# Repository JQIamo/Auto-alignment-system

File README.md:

# Source Code for Autoalignment System

This git repository contains the entire source code for the autoalignment
system described in {link to the paper}. It includes:

- `src/`: The firmware for the microcontroller (Teensy 4.1).
- `scripts/`: The python scripts, run on a host PC, to communicate with the microcontroller
  for manual control and diagnostic purposes.
- `calibration/`: A Jupyter notebook that calculate the $A$ matrix from calibration data.
-  `eagle/`: Eagle schematic and board files for fabricating the main control board and the detector boards.

Instructions for how to compile and use the source code are documented in each
individual folder.

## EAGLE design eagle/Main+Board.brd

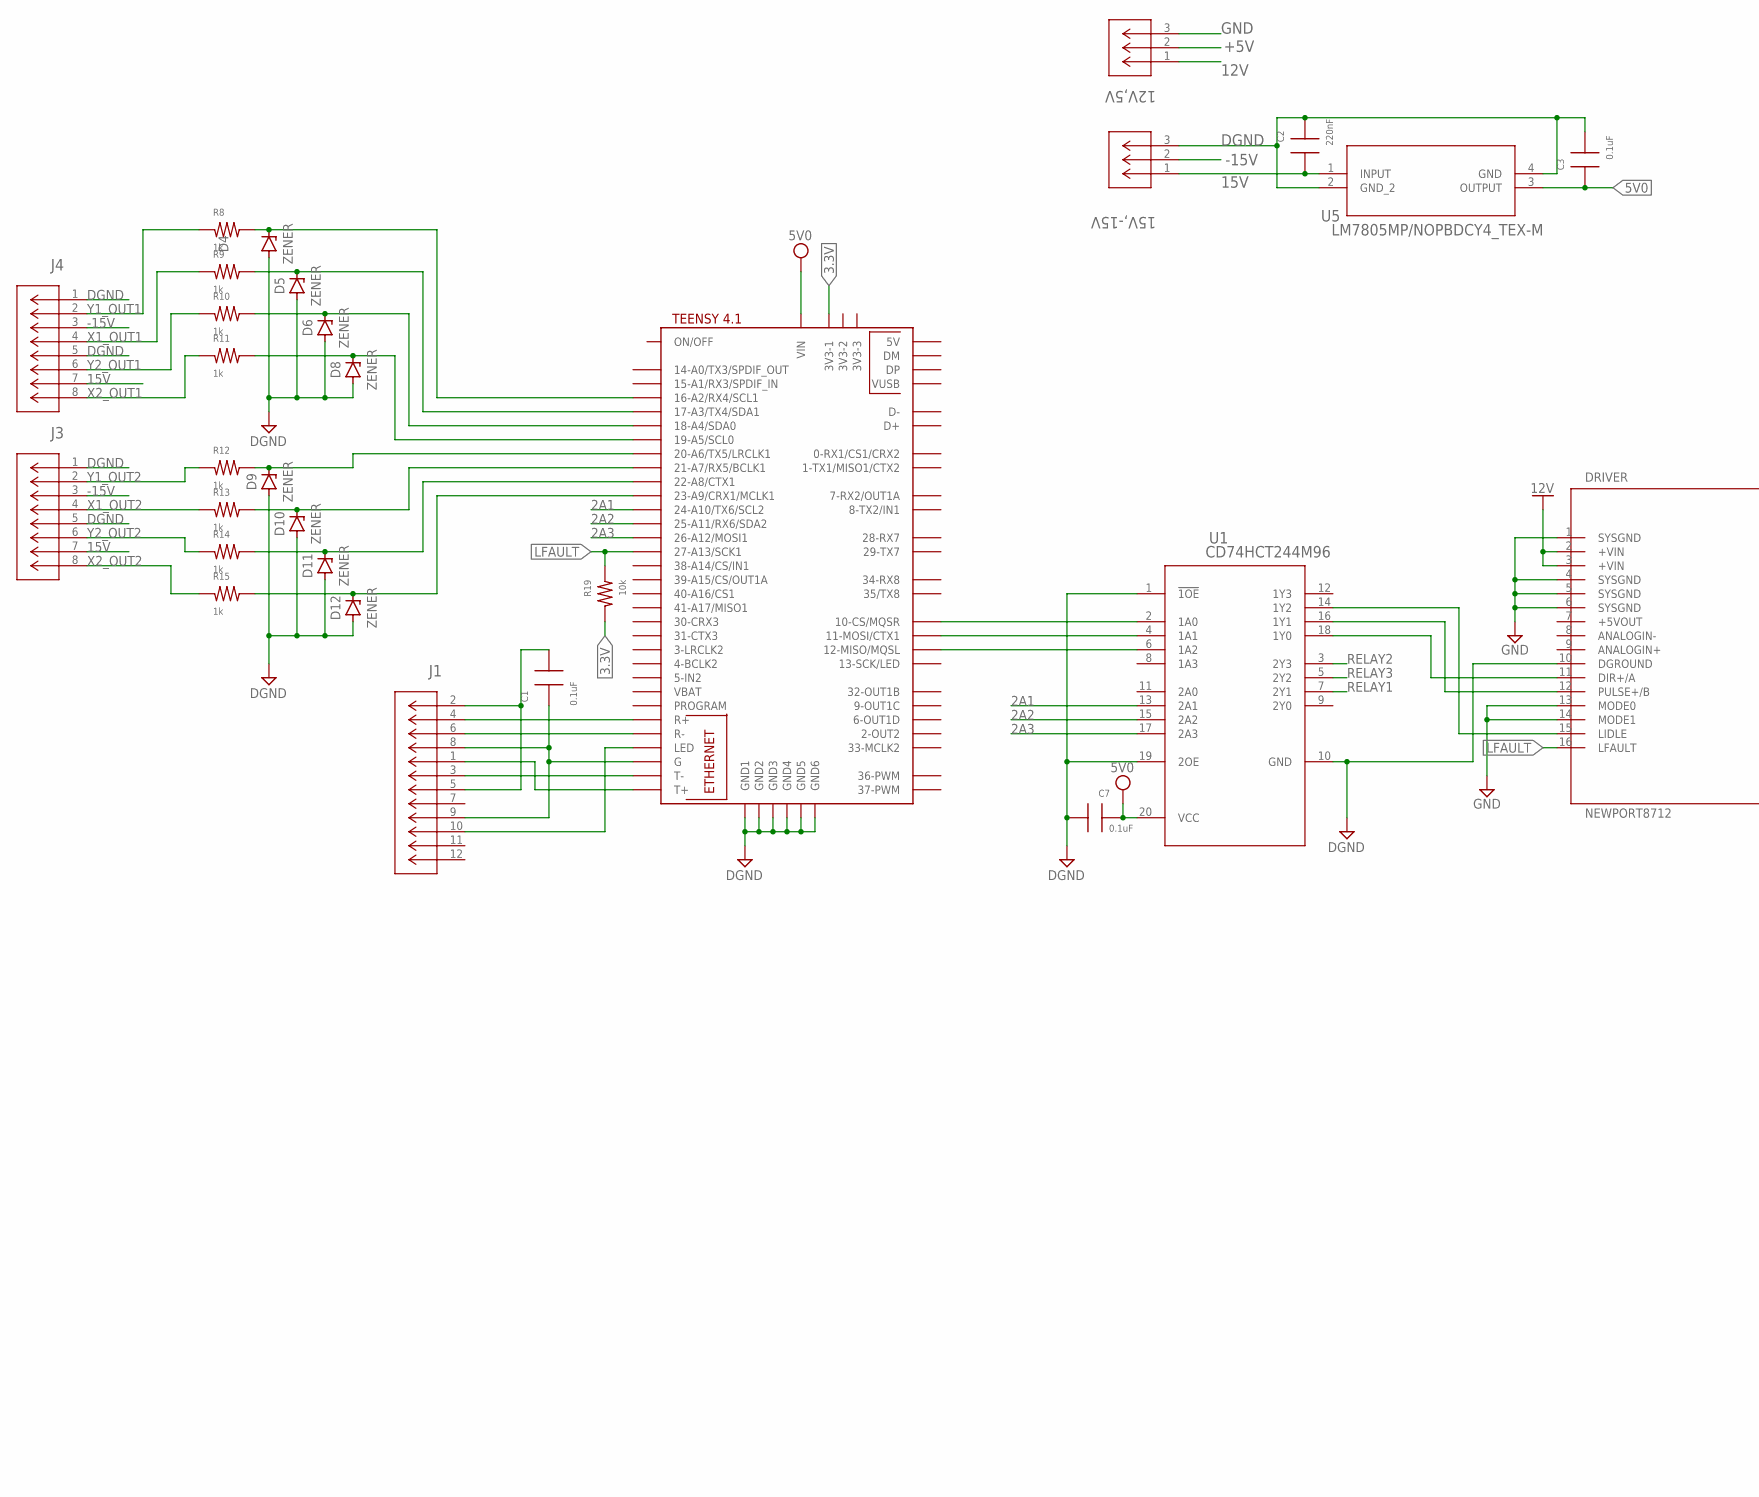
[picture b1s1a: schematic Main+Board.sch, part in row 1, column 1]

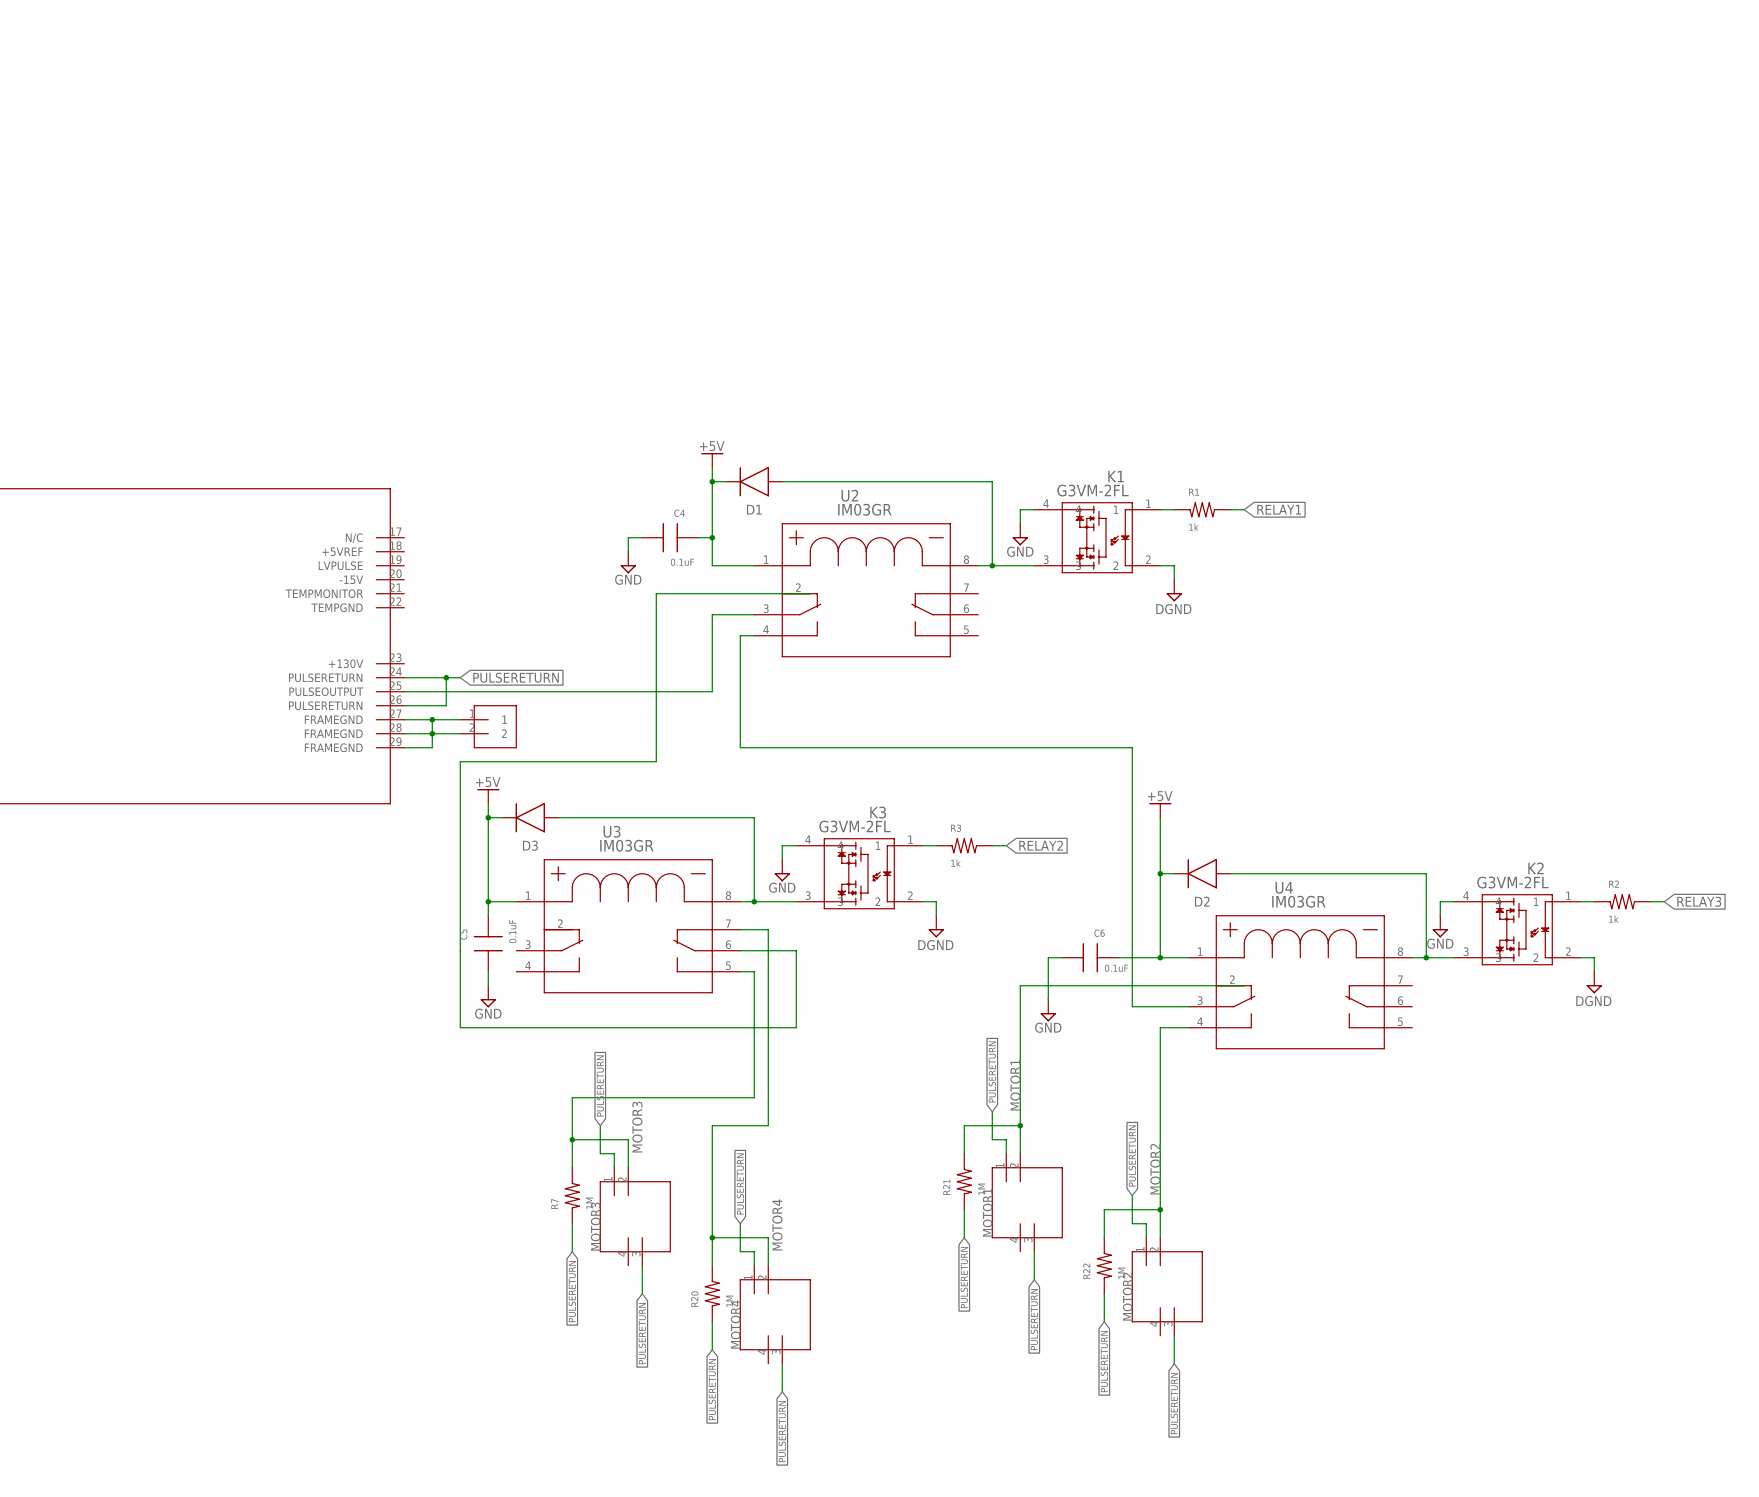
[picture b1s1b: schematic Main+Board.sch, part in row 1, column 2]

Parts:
12V,5V, 15V,-15V: 1729021; CONN_1729021_PXC; DIGIKEY 277-1237-ND
C1, C3, C4, C5, C6, C7: 0.1uF; 0603; DIGIKEY 478-7018-1-ND
C2: 220nF; 0603; DIGIKEY 732-7991-1-ND
D1, D2, D3: 1N4448W; SOD3715X135; DIGIKEY 2721-1N4148WTR-ND
D4, D5, D6, D8, D9, D10, D11, D12: ZENER; SODFL3718X115; DIGIKEY 846-KDZVTR3.3BCT-ND
DRIVER: NEWPORT8712
J1: J1B1211CCD; CONN12_J1B1211CCD_WIZ; DIGIKEY 1278-1052-ND
J3, J4: 75869-332LF; CONN_332LF_AMP; DIGIKEY 609-5123-ND
K1, K2, K3: G3VM-2FL; A-DIP4_THD_OMR; DIGIKEY Z2711-ND
MOTOR1, MOTOR2, MOTOR3, MOTOR4: TM5RJ3-44; DIGIKEY H11287-ND
R1, R2, R3, R8, R9, R10, R11, R12, R13, R14, R15: 1k; 0603; DIGIKEY P123733CT-ND
R7, R20, R21, R22: 1M; 1210; DIGIKEY 13-RC1210FR-071MLCT-ND
R19: 10k; 0603; DIGIKEY YAG1236CT-ND
U1: CD74HCT244M96; DW20; DIGIKEY 296-14552-1-ND
U2, U3, U4: IM03GR; RELAY8-239X396_230; DIGIKEY PB1061CT-ND
U5: LM7805MP/NOPBDCY4_TEX-M; DCY4_TEX-M; DIGIKEY 296-44517-1-ND
U$1: TEENSY41; DIGIKEY 1568-DEV-16771-ND
U$2: 360272; DIGIKEY 1849-1246-ND

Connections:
2A1: U1.13 (2A1), U$1.24-A10/TX6/SCL2
2A2: U1.15 (2A2), U$1.25-A11/RX6/SDA2
2A3: U1.17 (2A3), U$1.26-A12/MOSI1
3.3V: R19.2, U$1.3V3-1
5V0: C3.1, C7.2, U1.20 (VCC), U5.3 (OUTPUT), U$1.VIN
12V: 12V,5V.1, DRIVER.2 (+VIN), DRIVER.3 (+VIN)
15V: 15V,-15V.1, C2.1, J3.7, J4.7, U5.1 (INPUT)
+5V: 12V,5V.2, C4.2, C5.2, C6.2, D1.1 (C), D2.1 (C), D3.1 (C), U2.1, U3.1, U4.1
-15V: 15V,-15V.2, J3.3, J4.3
DGND: 15V,-15V.3, C2.2, C3.2, C7.1, D4.2 (A), D5.2 (A), D6.2 (A), D8.2 (A), D9.2 (A), D10.2 (A), D11.2 (A), D12.2 (A), DRIVER.10 (DGROUND), J3.1, J3.5, J4.1, J4.5, K1.2, K2.2, K3.2, U1.1 (!1OE), U1.10 (GND), U1.19 (2OE), U5.2 (GND_2), U5.4 (GND), U$1.GND1, U$1.GND2, U$1.GND3, U$1.GND4, U$1.GND5, U$1.GND6
FRAMEGND: DRIVER.27 (FRAMEGND), DRIVER.28 (FRAMEGND), DRIVER.29 (FRAMEGND), U$2.1, U$2.2
GND: 12V,5V.3, C4.1, C5.1, C6.1, DRIVER.1 (SYSGND), DRIVER.4 (SYSGND), DRIVER.5 (SYSGND), DRIVER.6 (SYSGND), DRIVER.13 (MODE0), DRIVER.14 (MODE1), K1.4, K2.4, K3.4
LFAULT: DRIVER.16 (LFAULT), R19.1, U$1.27-A13/SCK1
MOTOR1: MOTOR1.2, R21.2, U4.2
MOTOR2: MOTOR2.2, R22.2, U4.4
MOTOR3: MOTOR3.2, R7.2, U3.5
MOTOR4: MOTOR4.2, R20.2, U3.7
unnamed: D10.1 (C), R13.2, U$1.21-A7/RX5/BCLK1
unnamed: K1.1, R1.1
unnamed: D4.1 (C), R8.2, U$1.16-A2/RX4/SCL1
unnamed: D5.1 (C), R9.2, U$1.17-A3/TX4/SDA1
unnamed: D6.1 (C), R10.2, U$1.18-A4/SDA0
unnamed: D8.1 (C), R11.2, U$1.19-A5/SCL0
unnamed: U1.2 (1A0), U$1.10-CS\MQSR (10-CS/MQSR)
unnamed: U1.4 (1A1), U$1.11-MOSI/CTX1
unnamed: U1.6 (1A2), U$1.12-MISO/MQSL
unnamed: K2.1, R2.1
unnamed: K3.1, R3.1
unnamed: C1.2, J1.2, J1.5
unnamed: DRIVER.15 (LIDLE), U1.14 (1Y2)
unnamed: DRIVER.12 (PULSE+/B), U1.16 (1Y1)
unnamed: DRIVER.11 (DIR+/A), U1.18 (1Y0)
unnamed: D3.2 (A), K3.3, U3.8
unnamed: D9.1 (C), R12.2, U$1.20-A6/TX5/LRCLK1
unnamed: U2.2, U3.6
unnamed: U2.4, U4.3
unnamed: D1.2 (A), K1.3, U2.8
unnamed: D2.2 (A), K2.3, U4.8
unnamed: D12.1 (C), R15.2, U$1.23-A9/CRX1/MCLK1
unnamed: D11.1 (C), R14.2, U$1.22-A8/CTX1
unnamed: C1.1, J1.8, J1.9, U$1.G
unnamed: J1.10, U$1.LED
PULSEOUTPUT: DRIVER.25 (PULSEOUTPUT), U2.3
PULSERETURN: DRIVER.24 (PULSERETURN), DRIVER.26 (PULSERETURN), MOTOR1.1, MOTOR1.3, MOTOR2.1, MOTOR2.3, MOTOR3.1, MOTOR3.3, MOTOR4.1, MOTOR4.3, R7.1, R20.1, R21.1, R22.1
RELAY1: R1.2, U1.7 (2Y1)
RELAY2: R3.2, U1.3 (2Y3)
RELAY3: R2.2, U1.5 (2Y2)
R_N: J1.6, U$1.R-
R_P: J1.4, U$1.R+
T_N: J1.3, U$1.T-
T_P: J1.1, U$1.T+
X1_OUT1: J4.4, R9.1
X1_OUT2: J3.4, R13.1
X2_OUT1: J4.8, R11.1
X2_OUT2: J3.8, R15.1
Y1_OUT1: J4.2, R8.1
Y1_OUT2: J3.2, R12.1
Y2_OUT1: J4.6, R10.1
Y2_OUT2: J3.6, R14.1

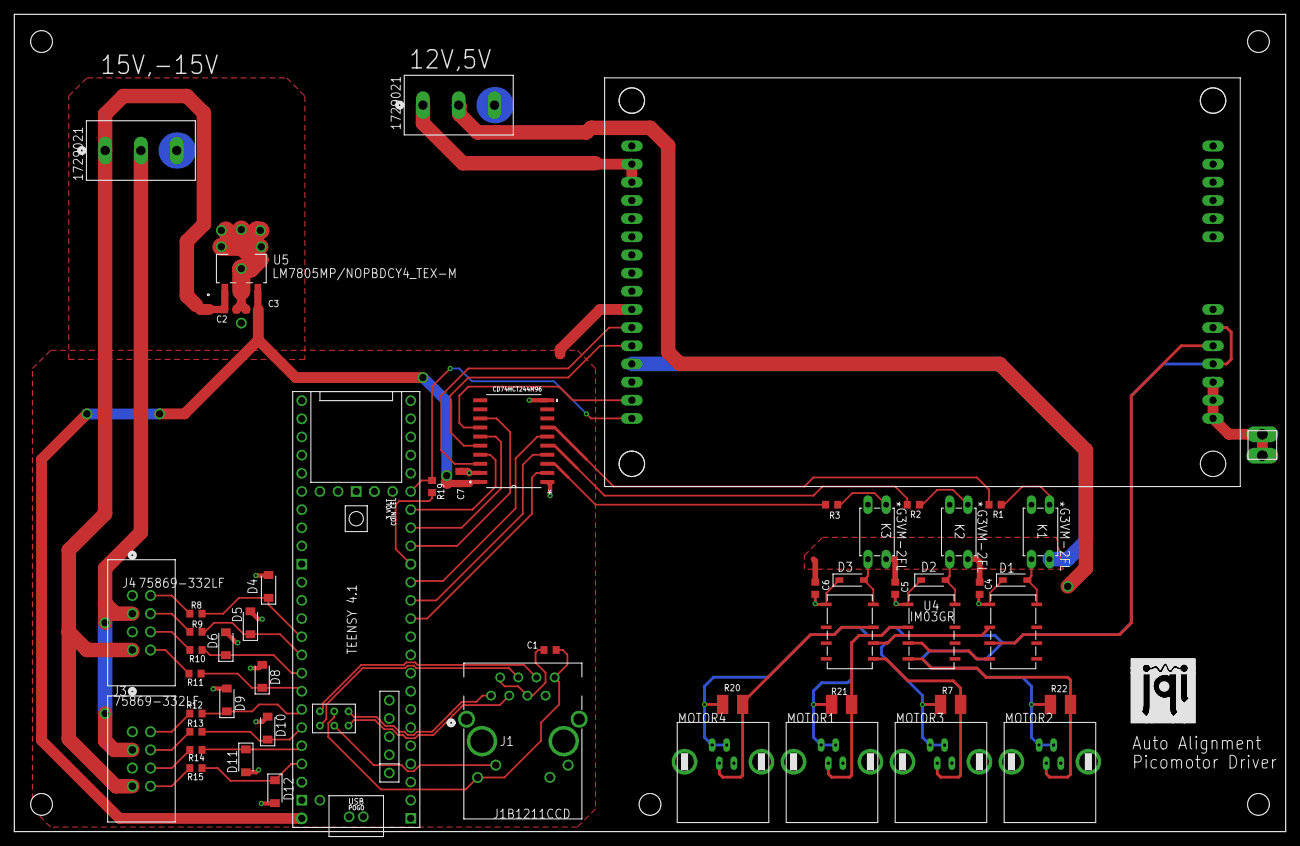
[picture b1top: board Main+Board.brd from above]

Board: 2 copper layers, 177.8 x 114.3 mm, 56 parts (0 on the bottom side), 59 nets.

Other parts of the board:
LOGO1: JQI-LOGOSILK; JQI_LOGO_NEGATIVE-SILKSCREEN@1
U$3: AUTOALIGNMENT

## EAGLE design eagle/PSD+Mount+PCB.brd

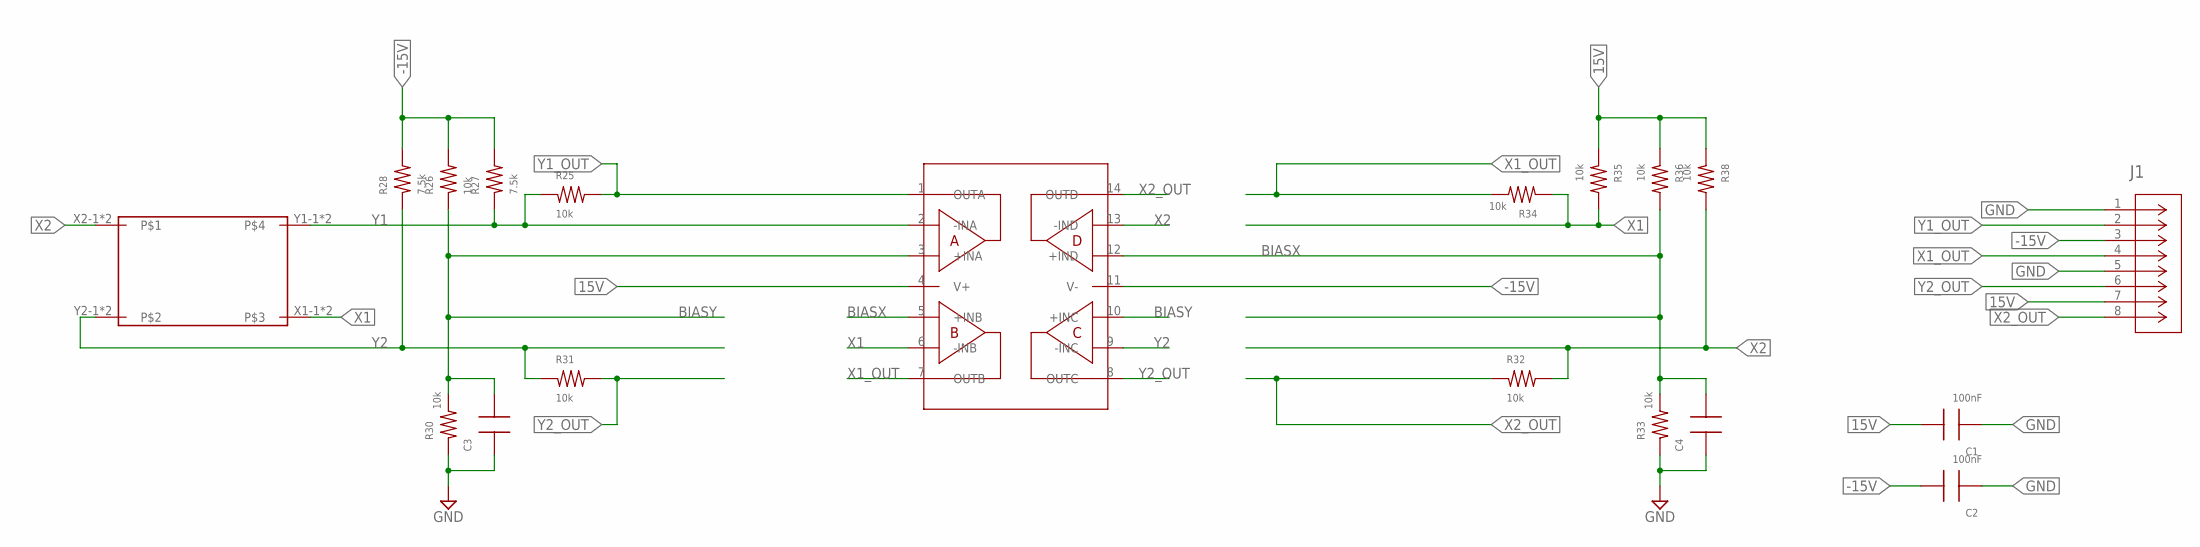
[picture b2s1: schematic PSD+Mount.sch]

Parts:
AMP1: OPA4140; SOP65P640X120-14N; DIGIKEY 296-46322-1-ND
C1, C2: 100nF; 0603; DIGIKEY 478-7018-1-ND
C3, C4: CAP0603; 0603; DIGIKEY 478-7018-1-ND
J1: 75869-332LF; CONN_332LF_AMP; DIGIKEY 609-5123-ND
R25, R26, R30, R31, R32, R33, R34, R35, R36, R38: 10k; 0603; DIGIKEY YAG1236CT-ND
R27, R28: 7.5k; 0603; DIGIKEY YAG1236CT-ND
U$1: 2L10UV_SU7

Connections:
15V: AMP1.4 (V+), C1.2, J1.7, R35.1, R36.1, R38.1
-15V: AMP1.11 (V-), C2.2, J1.3, R26.2, R27.2, R28.2
BIASX: AMP1.5 (+INB), AMP1.12 (+IND), C4.2, R33.2, R36.2
BIASY: AMP1.3 (+INA), AMP1.10 (+INC), C3.2, R26.1, R30.2
GND: C1.1, C2.1, C3.1, C4.1, J1.1, J1.5, R30.1, R33.1
X1: AMP1.6 (-INB), R34.1, R35.2, U$1.X1-1, U$1.X1-2
X1_OUT: AMP1.7 (OUTB), J1.4, R34.2
X2: AMP1.13 (-IND), R32.2, R38.2, U$1.X2-1, U$1.X2-2
X2_OUT: AMP1.14 (OUTD), J1.8, R32.1
Y1: AMP1.2 (-INA), R25.1, R27.1, U$1.Y1-1, U$1.Y1-2
Y1_OUT: AMP1.1 (OUTA), J1.2, R25.2
Y2: AMP1.9 (-INC), R28.1, R31.1, U$1.Y2-1, U$1.Y2-2
Y2_OUT: AMP1.8 (OUTC), J1.6, R31.2

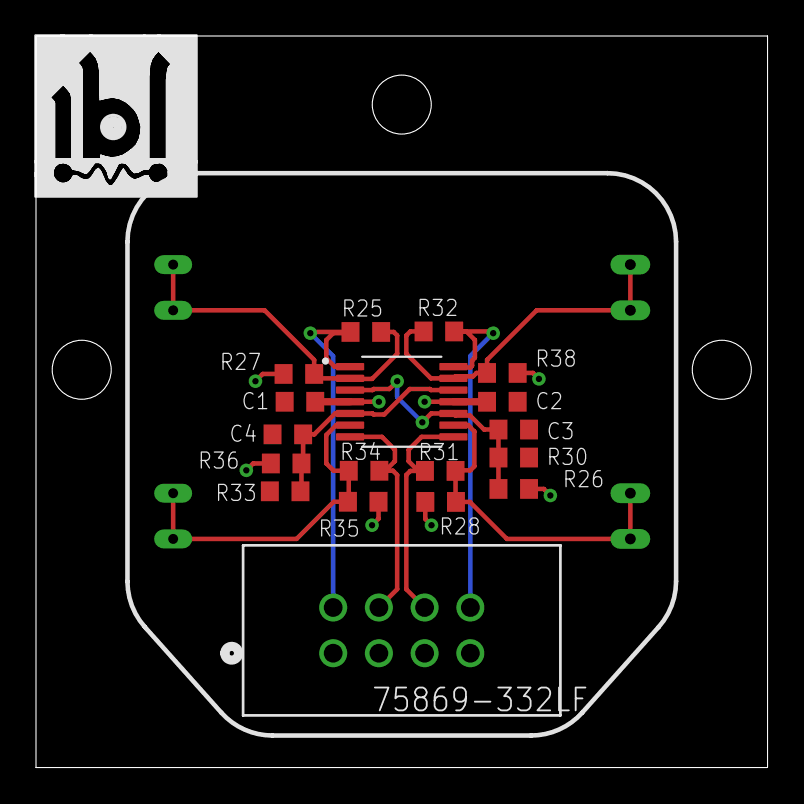
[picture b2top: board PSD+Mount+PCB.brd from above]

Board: 4 copper layers, 40.6 x 40.6 mm, 20 parts (1 on the bottom side), 13 nets.

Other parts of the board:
LOGO1: JQI-LOGOSILK; JQI_LOGO_NEGATIVE-SILKSCREEN@1

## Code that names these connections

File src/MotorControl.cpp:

#include "Arduino.h"
#include "arduino_freertos.h"

#include "MotorControl.h"

uint8_t current_motor;
bool motor_idle, motor_direction;


void moveMotors(const IntVector4 *motor_steps) {
	moveMotor(MIRROR1_X_MOTOR, (motor_steps->v[0] > 0), 800, abs(motor_steps->v[0]));
	moveMotor(MIRROR1_Y_MOTOR, (motor_steps->v[1] > 0), 800, abs(motor_steps->v[1]));
	moveMotor(MIRROR2_X_MOTOR, (motor_steps->v[2] > 0), 800, abs(motor_steps->v[2]));
	moveMotor(MIRROR2_Y_MOTOR, (motor_steps->v[3] > 0), 800, abs(motor_steps->v[3]));
}

void moveMotor(uint8_t motor, bool clockwise, uint32_t frequency, uint32_t step)
{
	::noTone(MOTOR_PULSE_PIN);

	if (motor != current_motor){
		switchMotor(motor);
	}

	if (motor_idle) {
		::digitalWriteFast(MOTOR_IDLE_PIN, arduino::HIGH);
		motor_idle = false;
		::vTaskDelay(pdMS_TO_TICKS(500));
	}

	if (motor_direction != clockwise){
		::digitalWriteFast(MOTOR_DIRECTION_PIN, (clockwise ? arduino::HIGH : arduino::LOW));
		motor_direction = clockwise;
		::vTaskDelay(pdMS_TO_TICKS(5));
	}

	uint32_t duration = 1000 * step / frequency;

	::Serial.printf("] Move m%d, direction %d, rate %d, step %d, duration %d\r\n", motor, clockwise, frequency, step, duration);

	if (duration > 0) {
		::tone(MOTOR_PULSE_PIN, frequency, duration); 
		::vTaskDelay(pdMS_TO_TICKS(duration));
	}
}

bool switchMotor(uint8_t motor)
{
	if (!motor_idle){
		::digitalWriteFast(MOTOR_IDLE_PIN, arduino::LOW);
		motor_idle = true;
		::vTaskDelay(pdMS_TO_TICKS(500));  // 500 ms is required by the datasheet to safely discharge picomotor.
	}

	if (motor >= MOTOR_CNT) return false;

	current_motor = motor;

	MotorAddr ma = motorAddrs[motor];
	::digitalWriteFast(RELAY1_PIN, ma.relay1);
	::digitalWriteFast(RELAY2_PIN, ma.relay2);
	::digitalWriteFast(RELAY3_PIN, ma.relay3);

	return true;
}

FLASHMEM __attribute__((noinline)) void initMotors() 
{
	::pinMode(RELAY1_PIN, arduino::OUTPUT);
	::pinMode(RELAY2_PIN, arduino::OUTPUT);
	::pinMode(RELAY3_PIN, arduino::OUTPUT);

	::pinMode(MOTOR_IDLE_PIN, arduino::OUTPUT);
	::pinMode(MOTOR_DIRECTION_PIN, arduino::OUTPUT);
	::pinMode(MOTOR_PULSE_PIN, arduino::OUTPUT);

	::digitalWriteFast(MOTOR_IDLE_PIN, arduino::LOW);
	motor_idle = true;
	::digitalWriteFast(MOTOR_DIRECTION_PIN, arduino::LOW);
	motor_direction = false;
}

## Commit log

2024-01-17 Add firmware code and util scripts.
2024-01-17 Add calibration notebook and data
2024-01-17 Add documentations.
2024-03-25 Added all the eagle files for PCB fabrication
2024-03-25 Update README.md with Eagle reference

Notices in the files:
parts and their libraries:
COPYRIGHT: Copyright (C) 2018 Accelerated Designs. All rights reserved
COPYRIGHT: Copyright (C) 2016 Accelerated Designs. All rights reserved
